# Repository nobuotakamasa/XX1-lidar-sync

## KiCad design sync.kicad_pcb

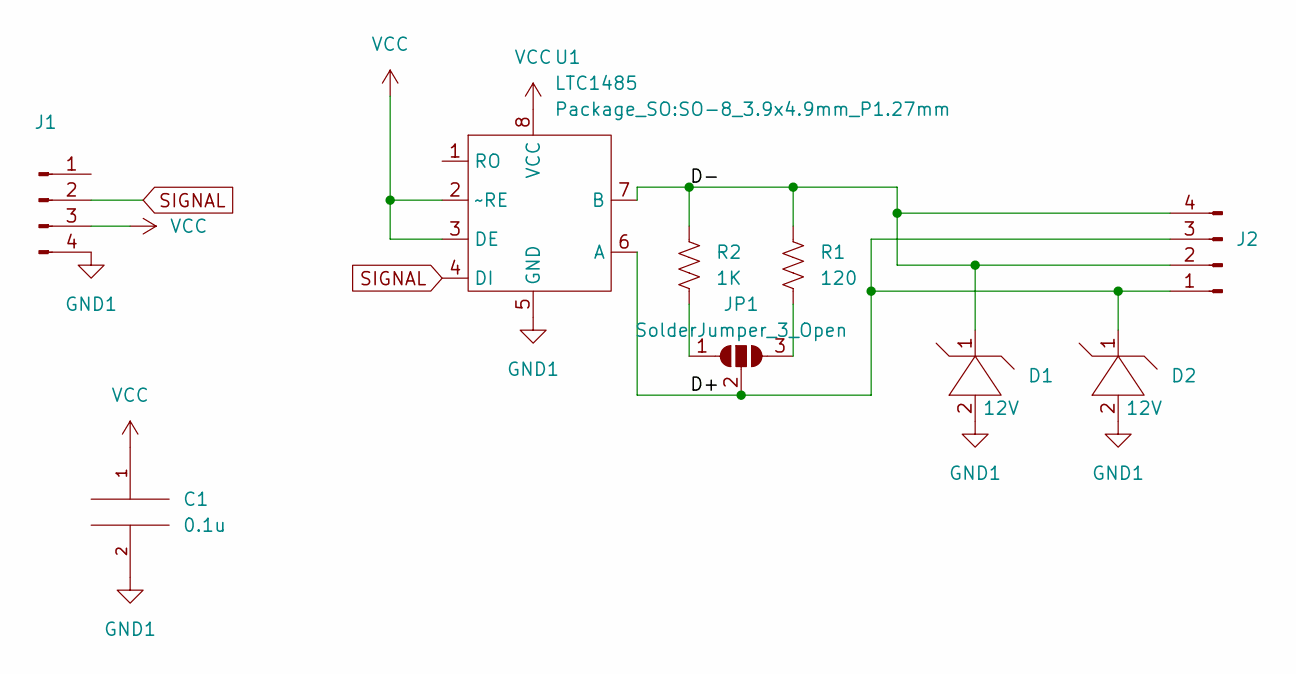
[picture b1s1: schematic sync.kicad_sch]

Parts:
C1: 0.1u; C_0603_1608Metric_Pad1.08x0.95mm_HandSolder
D1, D2: 12V; SMA (DO-214AC)
J1: Conn_01x04_Male; PinHeader_1x04_P2.54mm_Vertical
J2: Conn_01x04_Male; JST_XA_S04B-XASK-1N-BN_1x04_P2.50mm_Horizontal
JP1: SolderJumper_3_Open; SolderJumper-3_P1.3mm_Open_Pad1.0x1.5mm
R1: 120; R_0603_1608Metric
R2: 1K; R_0603_1608Metric
U1: LTC1485; SO-8_3.9x4.9mm_P1.27mm

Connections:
/D+: D2.1, J2.1, J2.3, JP1.2 (C), U1.6 (A)
/D-: D1.1, J2.2, J2.4, R1.1, R2.1, U1.7 (B)
GND1: C1.2, D1.2, D2.2, J1.4, U1.5 (GND)
unnamed: JP1.1 (A), R2.2
unnamed: JP1.3 (B), R1.2
SIGNAL: J1.2, U1.4 (DI)
VCC: C1.1, J1.3, U1.2 (~RE), U1.3 (DE), U1.8 (VCC)

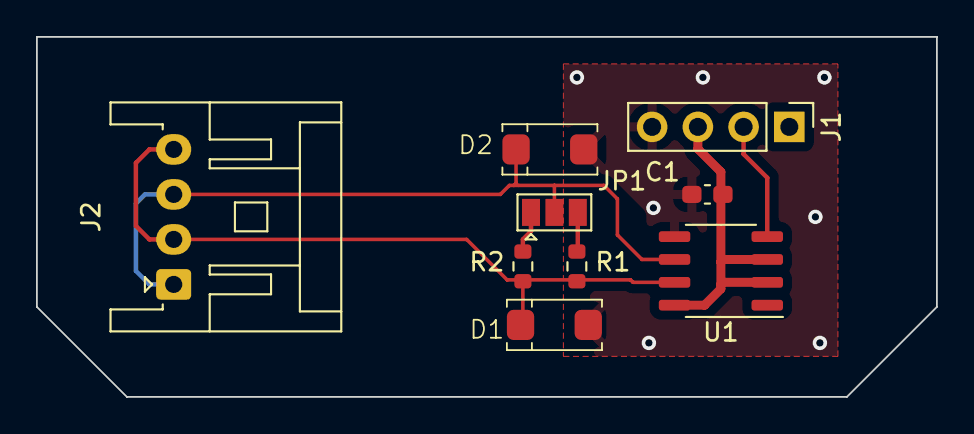
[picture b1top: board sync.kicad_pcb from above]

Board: 2 copper layers, 50.0 x 20.0 mm, 9 parts (0 on the bottom side), 7 nets.

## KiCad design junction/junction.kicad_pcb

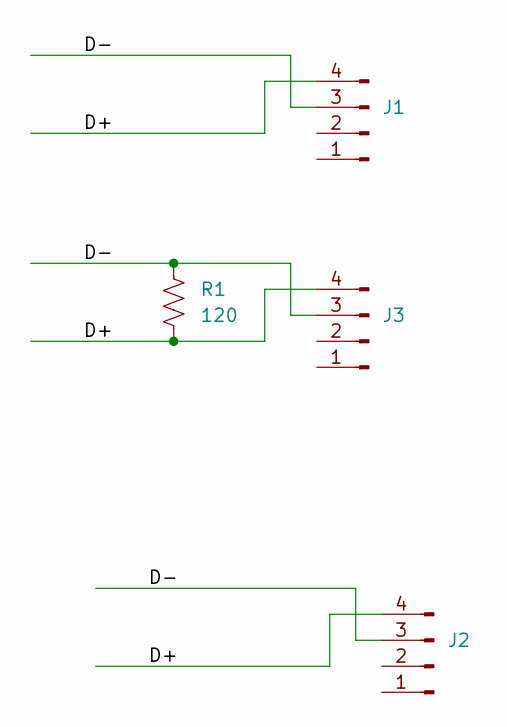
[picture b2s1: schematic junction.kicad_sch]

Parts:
J1, J2, J3: Conn_01x04_Male; JST_XA_S04B-XASK-1N-BN_1x04_P2.50mm_Horizontal
R1: 120; R_0603_1608Metric

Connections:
/D+: J1.4, J2.4, J3.4, R1.2
/D-: J1.3, J2.3, J3.3, R1.1

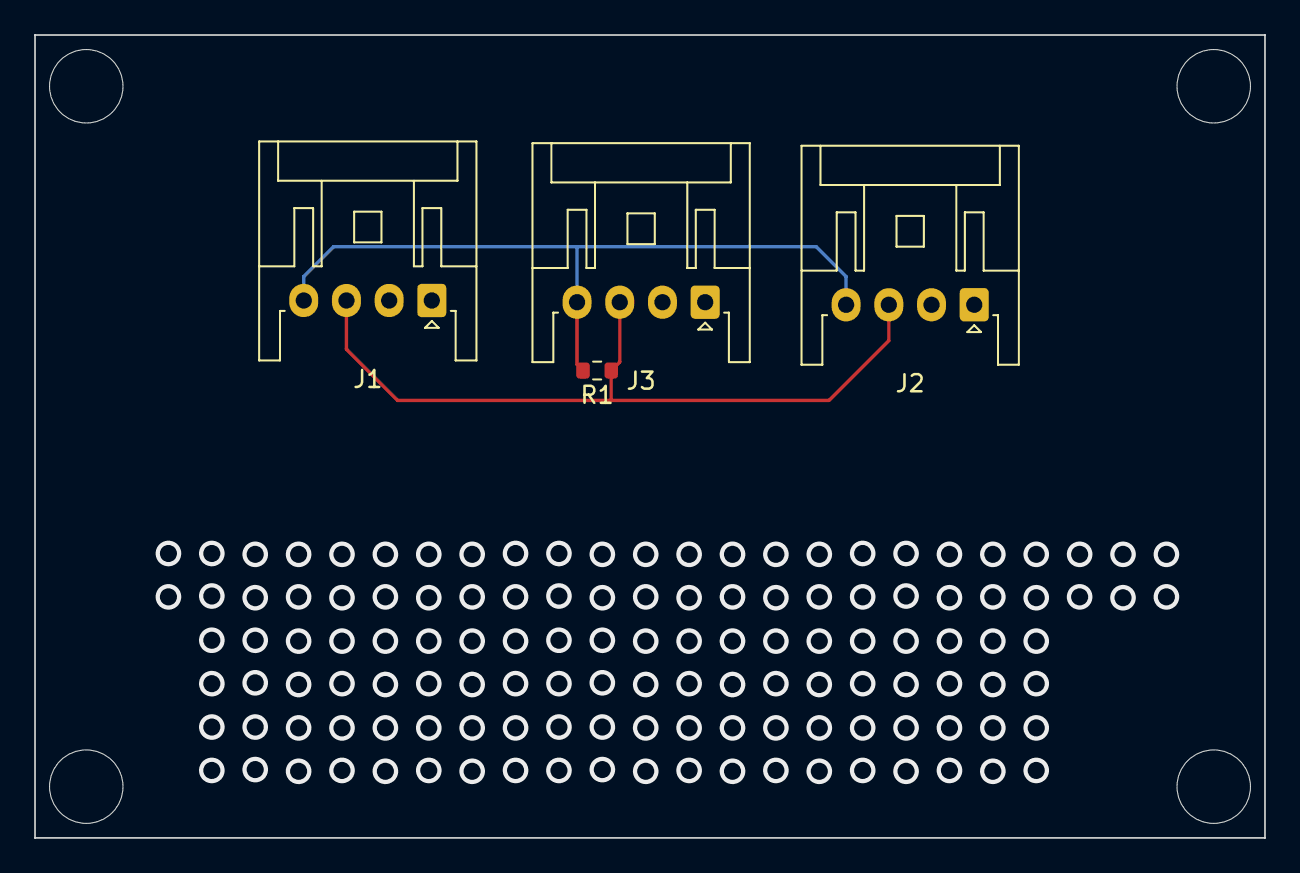
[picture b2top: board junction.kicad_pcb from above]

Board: 2 copper layers, 72.0 x 47.0 mm, 4 parts (0 on the bottom side), 2 nets.

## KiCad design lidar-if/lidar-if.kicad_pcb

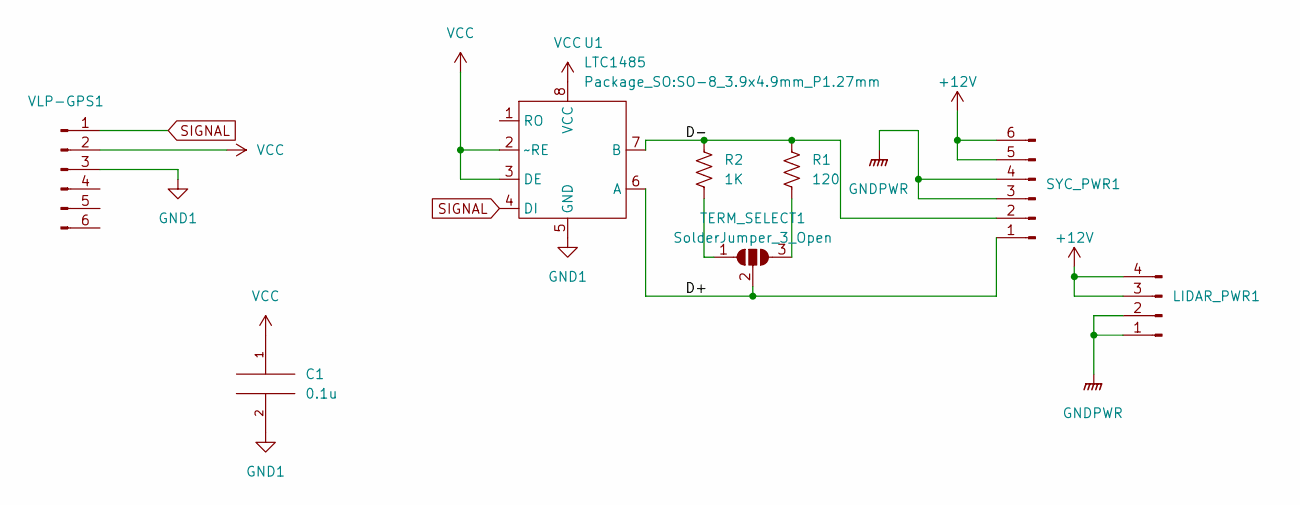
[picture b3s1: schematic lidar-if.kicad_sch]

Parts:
C1: 0.1u; C_0603_1608Metric
LIDAR_PWR1: Conn_01x04_Male; JST_XA_S04B-XASK-1N-BN_1x04_P2.50mm_Horizontal
R1: 120; R_0603_1608Metric
R2: 1K; R_0603_1608Metric
SYC_PWR1: Conn_01x06_Pin; JST_XA_S06B-XASK-1N-BN_1x06_P2.50mm_Horizontal
TERM_SELECT1: SolderJumper_3_Open; SolderJumper-3_P1.3mm_Open_Pad1.0x1.5mm
U1: LTC1485; SO-8_3.9x4.9mm_P1.27mm
VLP-GPS1: Conn_01x06_Pin; JST_SH_SM06B-SRSS-TB_1x06-1MP_P1.00mm_Horizontal

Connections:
+12V: LIDAR_PWR1.3, LIDAR_PWR1.4, SYC_PWR1.5, SYC_PWR1.6
/D+: SYC_PWR1.1, TERM_SELECT1.2 (C), U1.6 (A)
/D-: R1.1, R2.1, SYC_PWR1.2, U1.7 (B)
GND1: C1.2, U1.5 (GND), VLP-GPS1.3
GNDPWR: LIDAR_PWR1.1, LIDAR_PWR1.2, SYC_PWR1.3, SYC_PWR1.4
unnamed: R2.2, TERM_SELECT1.1 (A)
unnamed: R1.2, TERM_SELECT1.3 (B)
SIGNAL: U1.4 (DI), VLP-GPS1.1
VCC: C1.1, U1.2 (~RE), U1.3 (DE), U1.8 (VCC), VLP-GPS1.2

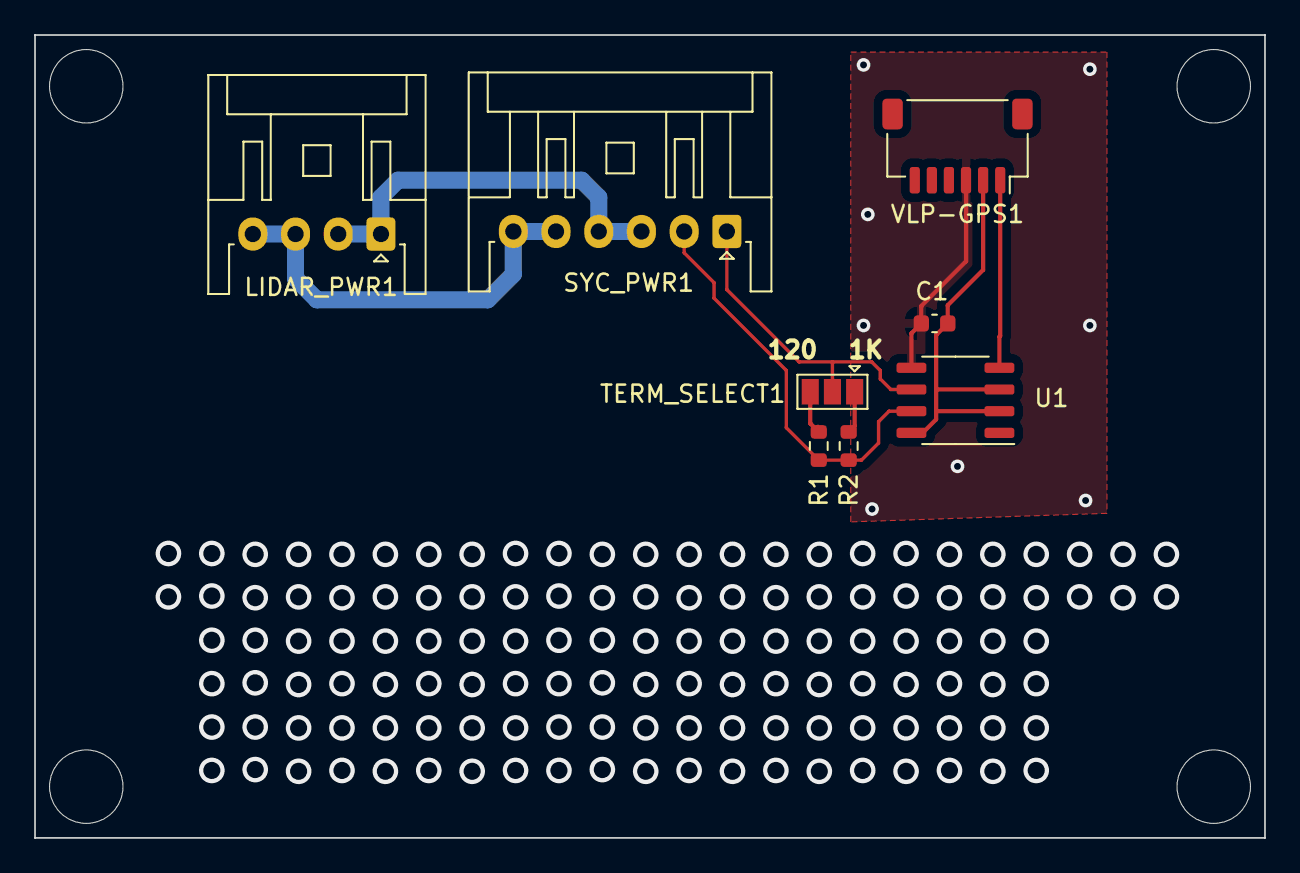
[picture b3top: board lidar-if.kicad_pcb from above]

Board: 2 copper layers, 72.0 x 47.0 mm, 8 parts (0 on the bottom side), 9 nets.

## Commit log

2023-05-15 place route
2023-05-22 add lidar-if
2023-05-22 modify
2023-05-26 Bump tj-actions/changed-files from 35 to 36
    Bumps [tj-actions/changed-files](https://github.com/tj-actions/changed-files) from 35 to 36.
    - [Release notes](https://github.com/tj-actions/changed-files/releases)
    - [Changelog](https://github.com/tj-actions/changed-files/blob/main/HISTORY.md)
    - [Commits](https://github.com/tj-actions/changed-files/compare/v35...v36)
    ---
    updated-dependencies:
2023-05-30 backup
2023-05-30 add gerber
2023-05-31 bug fix
2023-06-05 gerber
2023-06-26 Bump tj-actions/changed-files from 35 to 37
    Bumps [tj-actions/changed-files](https://github.com/tj-actions/changed-files) from 35 to 37.
    - [Release notes](https://github.com/tj-actions/changed-files/releases)
    - [Changelog](https://github.com/tj-actions/changed-files/blob/main/HISTORY.md)
    - [Commits](https://github.com/tj-actions/changed-files/compare/v35...v37)
    ---
    updated-dependencies:
2023-08-23 Bump tj-actions/changed-files from 35 to 38
    Bumps [tj-actions/changed-files](https://github.com/tj-actions/changed-files) from 35 to 38.
    - [Release notes](https://github.com/tj-actions/changed-files/releases)
    - [Changelog](https://github.com/tj-actions/changed-files/blob/main/HISTORY.md)
    - [Commits](https://github.com/tj-actions/changed-files/compare/v35...v38)
    ---
    updated-dependencies:
